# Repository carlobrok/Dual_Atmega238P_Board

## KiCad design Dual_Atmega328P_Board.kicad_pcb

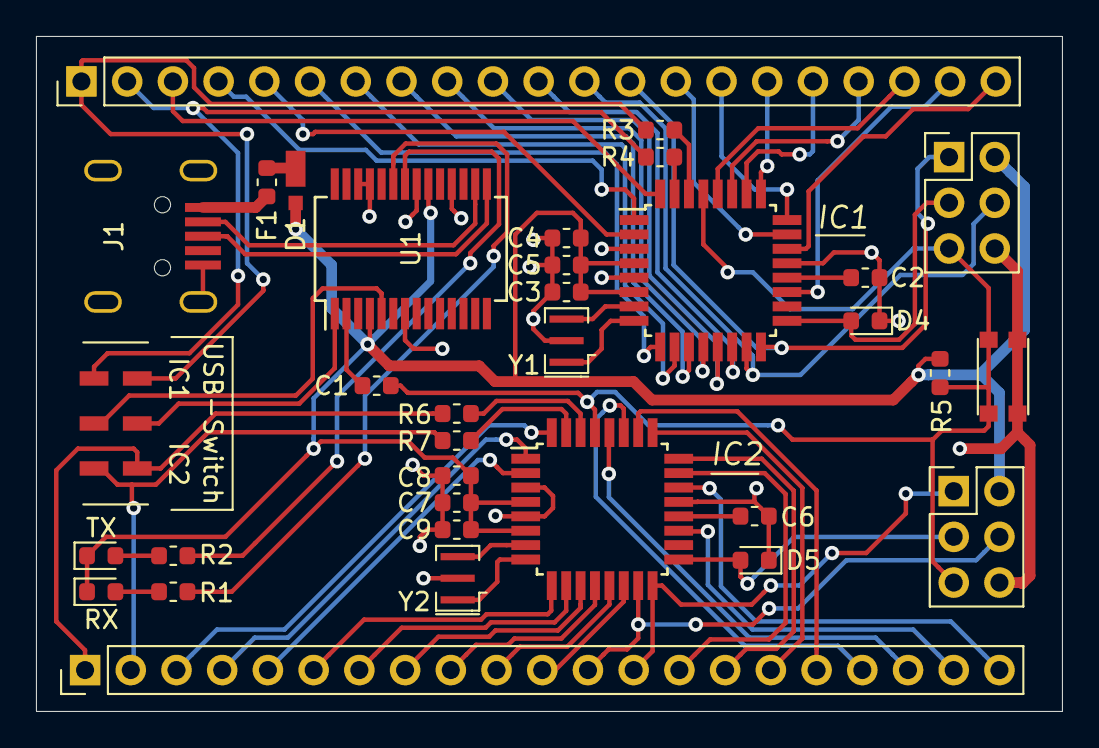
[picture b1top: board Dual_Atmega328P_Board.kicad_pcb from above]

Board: 2 copper layers, 57.0 x 37.5 mm, 34 parts (0 on the bottom side), 68 nets.

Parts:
C1, C2, C6: 100nF; C_0603_1608Metric
C3, C5, C7, C9: 1µF; C_0603_1608Metric
C4, C8: 4,7µF; C_0603_1608Metric
D1: SS1P3L; Diode_Shottky_Vishay_MSS1P3L
D4, D5: DEBUG_LED; LED_0603_1608Metric
F1: Polyfuse; Fuse_0603_1608Metric
IC1, IC2: ATmega328P-AU; TQFP-32_7x7mm_P0.8mm
J1: USB_B_Mini; USB_Mini_Hirose_UX60-MB-5S8
J2, J3: Conn_02x03_Odd_Even; PinHeader_2x03_P2.54mm_Vertical
J4, J5: Conn_01x21; PinHeader_1x21_P2.54mm_Vertical
R1, R2, R3, R4, R5, R6, R7: 1k; R_0603_1608Metric
RX: RX; LED_0603_1608Metric
SW1: SW_Push_DPDT; SW_CK_JS202011JCQN
SW2: RESET; SW_CK_SPST_KMR7
TX: TX; LED_0603_1608Metric
U1: FT232RL; SSOP-28_5.3x10.2mm_P0.65mm
Y1, Y2: CSTNE16M0VH3C000R0; Resonator_SMD_muRata_CSTxExxV-3Pin_3.0x1.1mm

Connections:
+5V: C3.1, C4.1, C5.1, C7.1, C8.1, C9.1, D1.1, IC1.4, IC1.6, IC2.4, IC2.6, J2.2, J3.2, R5.1, RX.1, TX.1, U1.4, U1.20
/A0_1: IC1.23, J5.14
/A0_2: IC2.23, J4.14
/A1_1: IC1.24, J5.15
/A1_2: IC2.24, J4.15
/A2_1: IC1.25, J5.16
/A2_2: IC2.25, J4.16
/A3_1: IC1.26, J5.17
/A3_2: IC2.26, J4.17
/A4_1: IC1.27, J5.18
/A4_2: IC2.27, J4.18
/A5_1: IC1.28, J5.19
/A5_2: IC2.28, J4.19
/A6_1: IC1.19, J5.20
/A6_2: IC2.19, J4.20
/A7_1: IC1.22, J5.21
/A7_2: IC2.22, J4.21
/Atmega328P_1/D0_RX: IC1.30, R3.2
/Atmega328P_1/D1_TX: IC1.31, R4.2
/Atmega328P_1/D13_SCK: D4.2, IC1.17, J2.3
/Atmega328P_2/D0_RX: IC2.30, R6.2
/Atmega328P_2/D1_TX: IC2.31, R7.2
/Atmega328P_2/D13_SCK: D5.2, IC2.17, J3.3
/D2_1: IC1.32, J5.3
/D2_2: IC2.32, J4.3
/D3_1: IC1.1, J5.4
/D3_2: IC2.1, J4.4
/D4_1: IC1.2, J5.5
/D4_2: IC2.2, J4.5
/D5_1: IC1.9, J5.6
/D5_2: IC2.9, J4.6
/D6_1: IC1.10, J5.7
/D6_2: IC2.10, J4.7
/D7_1: IC1.11, J5.8
/D7_2: IC2.11, J4.8
/D8_1: IC1.12, J5.9
/D8_2: IC2.12, J4.9
/D9_1: IC1.13, J5.10
/D9_2: IC2.13, J4.10
/D10_1: IC1.14, J5.11
/D10_2: IC2.14, J4.11
/D11_1: IC1.15, J2.4, J5.12
/D11_2: IC2.15, J3.4, J4.12
/D12_1: IC1.16, J2.1, J5.13
/D12_2: IC2.16, J3.1, J4.13
/RESET: C1.1, IC1.29, IC2.29, J2.5, J3.5, R5.2, SW2.2
/RESET_USB: C1.2, U1.2
/RX_1: J5.1, R3.1, SW1.1
/RX_2: J4.1, R6.1, SW1.3
/RX_LED: R1.1, RX.2
/RX_USB: SW1.5, U1.5
/TX_1: J5.2, R4.1, SW1.4
/TX_2: J4.2, R7.1, SW1.6
/TX_LED: R2.1, TX.2
/TX_USB: SW1.2, U1.1
GND: C2.2, C3.2, C4.2, C5.2, C6.2, C7.2, C8.2, C9.2, D4.1, D5.1, IC1.3, IC1.5, IC1.21, IC2.3, IC2.5, IC2.21, J1.5, J1.6, J2.6, J3.6, SW2.1, U1.7, U1.18, U1.21, U1.25, U1.26, Y1.2, Y2.2
unnamed: C2.1, IC1.20
unnamed: C6.1, IC2.20
unnamed: D1.2, F1.1
unnamed: F1.2, J1.1
unnamed: J1.2, U1.16
unnamed: J1.3, U1.15
unnamed: R1.2, U1.23
unnamed: R2.2, U1.22
unnamed: IC1.7, Y1.3
unnamed: IC1.8, Y1.1
unnamed: IC2.7, Y2.3
unnamed: IC2.8, Y2.1

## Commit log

2019-11-25 Upload files
2019-11-29 Updated layout
